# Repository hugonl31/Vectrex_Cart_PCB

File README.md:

# Vectrex cartridge PCBs

**Homemade Vectrex cartridges: the boards, ready to order, and a 3D-printed shell.**

<p align="center">

<br>

</p>

Cartridge boards for the Vectrex (GCE / Milton Bradley, 1982), designed in KiCad 9 to burn your own games -
homebrew, your own builds, or replacements for the original GCE releases - and a shell to put them in. Every
board has its KiCad files, Gerbers for a board maker, 3D renders, its copper layers and a schematic.

**Author:** Hugo Bokhorst ([@hugonl31](https://github.com/hugonl31)), also the author of
[Vectrex_EMU](https://github.com/hugonl31/Vectrex_EMU), which emulates these boards (bank switching, the
512K flash with its latch).<br>
**Documentation, schematics and renders:** made with Claude (Anthropic).

## The boards

| | Board | Chip | Size | For |
|---|---|---|---|---|
|  | [64K](boards/v1_27c512_64k) | 27C512 / W27C512 + DS2431 | 32 or 64 KB | any game up to 64 KB, with PB6 bank switching and an optional save chip |
|  | [8K GCE](boards/v1_28c64_8k_gce) | 28C64 EEPROM | 8 KB | the original GCE releases (4 or 8 KB); keep its jumper on write-protect |
|  | [512K v2](boards/v2_512k_flash) | SST39SF040 flash + 74HC377 latch | 512 KB | big bank-switched games, saving into the flash |

All boards share one outline (54 x 66 mm, 1.6 mm, ENIG, bevelled edge fingers), so they all fit the
[shell](case).

## How a Vectrex cartridge works

The cartridge port is a 36-finger edge connector. The Vectrex's 6809 CPU sees the cartridge in a **32 KB
window, $0000-$7FFF**: address lines A0-A14 and data lines D0-D7 go straight to the memory chip, with /CE and
/OE. Most original games fit in 4 or 8 KB and simply repeat through the window.

Bigger games switch **banks**: they swap which part of a larger chip is in the window. The port carries one
line the game controls for that, **PB6** (finger 35) from the Vectrex's 6522 VIA; the 64K board puts it on the
chip's A15 (two 32 KB banks). The 512K board adds a latch: a write into $0000-$3FFF stores three more address
bits, A16-A18, for 16 banks - see its [README](boards/v2_512k_flash).

The port also has R/W (writes), /CART, /HALT, /NMI and /IRQ, +5 V and GND. The pinout, as the boards use it
(odd fingers on one side, even on the other):

| Finger | Signal | Finger | Signal | Finger | Signal | Finger | Signal |
|---|---|---|---|---|---|---|---|
| 1 | /HALT | 10 | A11 | 19 | D0 | 28 | GND |
| 2 | +5V | 11 | A3 | 20 | D6 | 29 | A12 |
| 3 | A7 | 12 | /OE | 21 | D1 | 30 | R/W |
| 4 | +5V | 13 | A2 | 22 | D5 | 31 | A13 |
| 5 | A6 | 14 | A10 | 23 | D2 | 32 | /CART |
| 6 | A8 | 15 | A1 | 24 | D4 | 33 | A14 |
| 7 | A5 | 16 | /CE | 25 | GND | 34 | /NMI |
| 8 | A9 | 17 | A0 | 26 | D3 | 35 | PB6 |
| 9 | A4 | 18 | D7 | 27 | GND | 36 | /IRQ |

## The schematics

The boards were drawn directly in KiCad's PCB editor, so there are no KiCad schematic sheets. Each board's
`images/schematic.svg` is drawn from the board file itself: every part with its pin names, each pin ending in
its net name (pins with the same name are connected). It always matches the board, because it is made from it.

## Making one

1. **Order the board:** upload the board's `*-gerbers.zip` to JLCPCB, PCBWay or similar. 1.6 mm; ENIG (gold)
   is worth it for the edge fingers; ask for the 45 degree bevel on the finger edge if they offer it.
2. **Program the chip** with a TL866 / T48 (XGecu) or similar - each board's README says how.
3. **Solder** it (all through-hole chips, 1206 passives: easy by hand) and **print the [shell](case)**.

## Repository

| Path | |
|---|---|
| `boards/` | one folder per board: KiCad files, Gerbers, `images/` (renders, copper, schematic), a README |
| `case/` | the shell's STL files and renders |
| `libs/` | the KiCad footprints and symbols the boards use (edge connector, mounting holes, Vectrex logos) |

Open a board's `.kicad_pro` in KiCad 9; its library tables point to `libs/`.

## License

The board designs, the shell and the documentation: [CERN-OHL-P-2.0](LICENSE.md) - use, change, make and sell
them, keep the notice. Vectrex and its logo are trademarks of their owners; this project is not affiliated
with them. Datasheets and vendor 3D models are not included (the boards use KiCad's standard models).

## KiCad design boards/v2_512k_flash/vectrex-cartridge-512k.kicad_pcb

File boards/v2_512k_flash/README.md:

# Vectrex cartridge v2.0 - 512 KB flash with a bank latch

**Schematic:** [images/schematic.svg](images/schematic.svg) (drawn from the board's own connections) -
**copper:** [front](images/pcb_front.svg), [back](images/pcb_back.svg).

(The renders show the flash with its maker's 3D model in the socket. KiCad has no PLCC-32 socket model, so this
repository has a simple one of its own, `libs/3d/PLCC-32_THT-Socket.wrl` (made by `libs/3d/socket_wrl.py`); the board
file uses it.)

Built from the v1 64K board (`../v1_27c512_64k`): the same outline, edge fingers, Vectrex
logos (front and back), mounting holes, GND fill and "THIS SIDE UP". 54 x 66 mm, 2 layers.

| File | |
|---|---|
| `vectrex-cartridge-512k.kicad_pcb` / `.kicad_pro` | the board (open in KiCad 9) |
| `vectrex-cartridge-512k-gerbers.zip` | Gerbers + drill files for the board maker (JLCPCB, PCBWay...) |
| `images/` | 3D renders, the copper layers (`pcb_front.svg`, `pcb_back.svg`) and the schematic |
| `make_board.py` | builds the board from v1 (parts, nets, placement) - KiCad's Python |
| `routing/` | the router used (own, 45 degree / bundled lanes) and its plan - see Routing below |
| `silk.py` | the part names on the silkscreen |

## Circuit

| Part | Connections |
|---|---|
| **U1** SST39SF040 (512 KB flash) in a PLCC-32 socket | A0-A14, D0-D7 from the cartridge port. **A15 = PB6** (port pin 35, as on v1), **A16 / A17 / A18 = U2 Q0 / Q1 / Q2**. /CE = port pin 16. /OE = U3 (below). /WE = JP2. |
| **U2** 74HC377 bank latch (SOIC-20W) | D1-D3 = data bus D0-D2, CLKEN (pin 1) = R/W (port 30), CLK (pin 11) = U4 (/CART OR A14). A write to $0000-$3FFF stores the bank number. 1Q-3Q = A16-A18. D4-D8 (pins 8, 13, 14, 17, 18) are tied to GND: their outputs 4Q-8Q are not used, and five fewer data branches leave room for tidy routing. |
| **U3** 74HC00 (SOIC-14) | gate 1: E = NAND(/OE pin 12, /OE pin 12); gate 2: flash /OE = NAND(E, R/W). The flash only drives the bus when the CPU reads - the datasheet (table 4-1) says that with /OE low it may drive the bus even during a write, which would fight the CPU writing the bank number. Gates 3 and 4: inputs to GND. |
| **U4** 74HC1G32 OR gate (SOT-23-5) | latch clock = /CART OR A14: only writes to the lower 16 KB ($0000-$3FFF) reach the latch (pin 1 /CART, 2 A14, 3 GND, 4 out, 5 +5 V). |
| **R1** 3.3K pull-up | on PB6 = A15, as v1: a defined bank from power-on. |
| **JP2** solder jumper (flash /WE) | printed bridge **1-2: /WE = R/W, the game can save into the flash** (default). Cut 1-2 and bridge 2-3: /WE to +5 V = write-protected. |
| **C1-C4** 100 nF | one per chip. |

No DS2431 any more: high scores and settings are saved in the flash itself.

### How the game switches banks

The cartridge window is 32 KB ($0000-$7FFF). Bank = A18 A17 A16 A15:

* **A15** is PB6 of the VIA, as on v1: `DDRB` bit 6 output + `ORB` bit 6 (input = pulled high = 1).
* **A16-A18**: write a byte to **any address in $0000-$3FFF**; its bits 0-2 become A16-A18 at the end of the
  write cycle. `sta $0000` with A = bank >> 1 is enough. Writes to $4000-$7FFF never change the bank.
* The 74HC377 has no reset: after power-on (and after the Vectrex RESET button) A16-A18 can be anything.
  So the boot code - the cartridge header at $0000 and the first instructions until the latch is written -
  must be the same in every bank where the game can start: all 8 latch values with PB6 = 1 (the 8 odd
  banks). A game made for the 64K board already keeps such a shared area in both of its banks; here it becomes 8 copies.
* Code that switches banks must run from a place that is the same in both banks (as now), or from RAM.

### Saving into the flash (high scores, settings)

The flash's commands are writes to $5555 and $2AAA (only A0-A14 count). With U4, $5555 (A14 = 1) never
clocks the latch, but $2AAA (A14 = 0) does, and its data byte is always `$55` = A16-A18 **101**. So during
every program and erase command the flash sees bank A16-A18 = 101 - always the same bank, so:

* Keep the save area in **$4000-$7FFF of a bank with A16-A18 = 101** (banks 10 and 11, by PB6), in its own
  4 KB sector(s) - nothing else in those sectors.
* Byte program: `$AA`->$5555, `$55`->$2AAA, `$A0`->$5555, data -> address (~20 us).
  Sector erase: `$AA`->$5555, `$55`->$2AAA, `$80`->$5555, `$AA`->$5555, `$55`->$2AAA, `$30`->sector (~25 ms).
* The code doing this must run from RAM (the flash can't be read while it's busy), with PB6 set for the save
  bank; finish by writing the game's bank number back to $0000-$3FFF.
* 100 000 erase cycles per sector, ~100 years retention. Use two sectors in turn with a counter + checksum, so
  a power cut in the middle of a save always leaves the previous save.
* JP2 2-3 makes the flash read-only (e.g. a collector's copy).

## Parts (digikey.at, October 2026)

| Ref | Part | DigiKey no. | Price |
|---|---|---|---|
| U1 | Microchip SST39SF040-55-4C-NHE-T (512 KB, PLCC-32, 55 ns) | SST39SF040-55-4C-NHE-TCT-ND | 2.58 EUR |
| U1 socket | Assmann A-CCS 032-Z-T (PLCC-32, through hole) | AE11106-ND | 1.86 EUR |
| U2 | TI SN74HC377DWR (SOIC-20W) - or SN74HCT377DW (see below) | 296-9818-1-ND | 0.76 EUR |
| U3 | TI SN74HC00DR (SOIC-14) - or SN74HCT00DR | search "SN74HC00DR" | 0.35 EUR |
| U4 | TI SN74AHCT1G32DBVR (SOT-23-5) | search "SN74AHCT1G32DBVR" | ~0.3 EUR |
| R1 | 3.3 kOhm 1206 | as v1 | |
| C1-C4 | 100 nF 1206 | as v1 | |
| | PLCC-32 to DIP-32 adapter for the XGecu programmer | AliExpress / eBay | |

**HC or HCT?** The 6809 and the VIA are NMOS chips: their "high" can be as low as 2.4 V, below what 74HC inputs
need at 5 V (3.5 V). In practice it usually works (they pull up close to 5 V with the light cartridge load), but
the HCT versions (TTL input levels, same pins, same price range) are the safe choice for all three logic chips.

The SST39SF020A (256 KB) and SST39SF010A (128 KB) fit the same socket: with them A18 (and A17) are not
connected inside the chip, the banks just repeat.

## Routing

The traces leave every edge finger straight up, then run as bundled lanes in 0 / 45 / 90 degree steps
with as few bends as possible; fingers without a function (/HALT 1, /NMI 34, /IRQ 36) have no copper at
all, and the two +5 V fingers (2 and 4) are joined by a wide track. The PLCC socket is turned 180 degrees
and placed 4 mm higher than in the first version, so the address bus reaches it from inside. GND: a fill
on both sides, joined by stitching vias wherever a piece of it would otherwise be cut off.

## Checks

* KiCad 9 DRC with the project's rules (0.152 mm clearance, +5 V and GND 0.254 mm / 0.61 mm tracks): no
  unconnected items, no clearance errors. Remaining, accepted (as v1): the edge fingers share one solder-mask
  opening; a silkscreen label touches a finger's pin number and JP2's "3" touches its pad; the edge connector's
  and KiCad library footprints' "differs from library" notes.
* Every piece of the GND fill (front and back) is tied to ground - checked with a connectivity pass over the
  pads, tracks, vias and fills.
* No vias under the back's parts legend.
* No tracks in the fingers' contact area (both sides): tracks only meet a finger at its top 1.6 mm.
* Pinouts checked against the datasheets: SST39SF040 (DS20005022, PLCC-32 = JEDEC numbering), SN74HC377
  (SCLS307D), SN74HC00 (SCLS181H).
* Timing to confirm on the first board: the latch clocks on /CART rising (end of the write); the 6809 holds
  the data ~30 ns after E falls, the 74HC377 needs ~5 ns hold - fine on paper, worth a first test with a
  bank-switch test cartridge before building more.

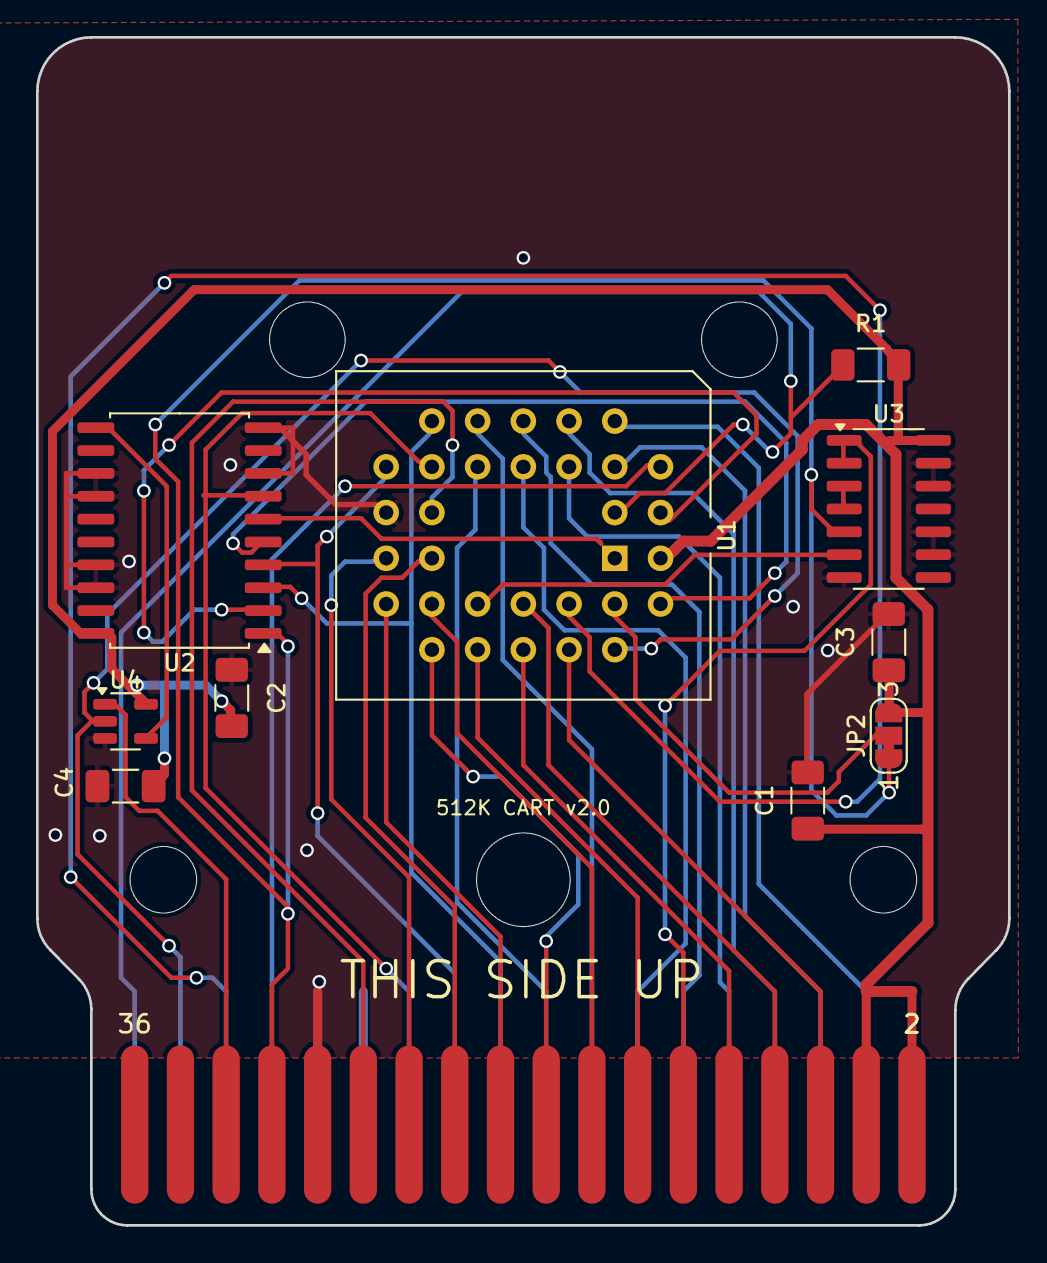
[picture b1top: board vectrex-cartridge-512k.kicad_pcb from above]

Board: 2 copper layers, 54.0 x 66.0 mm, 18 parts (1 on the bottom side), 37 nets.

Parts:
C1, C2, C3, C4: 100nF; C1_hand_1206_3216Metric_Pad1.33x1.80mm_HandSolder
CON1: vectrex-edge-connector; vectrex-edge-connector-thinner-no-soldermask
G1: LOGO; vectrex-us-soldermask
G3: LOGO; vectrex-uk-soldermask
H1, H3: 3.7mm; Mounting_Hole_D3.7mm
H2: 5.2mm; Mounting_Hole_D5.2mm
H4, H5: 4.2mm; Mounting_Hole_D4.2mm
JP2: FLASH /WE; SolderJumper-3_P1.3mm_Bridged12_RoundedPad1.0x1.5mm_NumberL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
R1: 3.3K; R1_1206_3216Metric_Pad1.30x1.75mm_HandSolder
U1: SST39SF040 (PLCC-32 socket); PLCC-32_THT-Socket
U2: 74HC377; SOIC-20W_7.5x12.8mm_P1.27mm
U3: 74HC00; SOIC-14_3.9x8.7mm_P1.27mm
U4: 74HC1G32; SOT-23-5

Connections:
+5V: C1.1, C2.1, C3.1, C4.1, CON1.2, CON1.4, JP2.3, R1.2, U1.32, U2.20, U3.14, U4.5
BA16: U1.2, U2.2
BA17: U1.30, U2.5
BA18: U1.1, U2.6
C_A0: CON1.17, U1.12
C_A1: CON1.15, U1.11
C_A2: CON1.13, U1.10
C_A3: CON1.11, U1.9
C_A4: CON1.9, U1.8
C_A5: CON1.7, U1.7
C_A6: CON1.5, U1.6
C_A7: CON1.3, U1.5
C_A8: CON1.6, U1.27
C_A9: CON1.8, U1.26
C_A10: CON1.14, U1.23
C_A11: CON1.10, U1.25
C_A12: CON1.29, U1.4
C_A13: CON1.31, U1.28
C_A14: CON1.33, U1.29, U4.2
C_D0: CON1.19, U1.13, U2.3
C_D1: CON1.21, U1.14, U2.4
C_D2: CON1.23, U1.15, U2.7
C_D3: CON1.26, U1.17
C_D4: CON1.24, U1.18
C_D5: CON1.22, U1.19
C_D6: CON1.20, U1.20
C_D7: CON1.18, U1.21
E: U3.3, U3.4
FL_OE: U1.24, U3.6
FL_WE: JP2.2, U1.31
GND: C1.2, C2.2, C3.2, C4.2, CON1.25, CON1.27, CON1.28, U1.16, U2.8, U2.10, U2.13, U2.14, U2.17, U2.18, U3.7, U3.9, U3.10, U3.12, U3.13, U4.3
LCLK: U2.11, U4.4
V-CART: CON1.32, U4.1
V-CE: CON1.16, U1.22
V-OE: CON1.12, U3.1, U3.2
V-PB6: CON1.35, R1.1, U1.3
V-RW: CON1.30, JP2.1, U2.1, U3.5

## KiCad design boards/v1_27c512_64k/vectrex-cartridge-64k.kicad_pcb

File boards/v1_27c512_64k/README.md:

# 64K cartridge - 27C512 / W27C512 with a DS2431 save chip

The main board: any Vectrex game up to 64 KB, on a 27C512 EPROM or a Winbond W27C512 (electrically erasable:
no UV lamp, the programmer erases it). 54 x 66 mm, 2 layers, 1.6 mm, ENIG, bevelled edge fingers.

**Schematic:** [images/schematic.svg](images/schematic.svg) (drawn from the board's own connections) -
**copper:** [front](images/pcb_front.svg), [back](images/pcb_back.svg).

| File | |
|---|---|
| `vectrex-cartridge-64k.kicad_pcb` / `.kicad_pro` | the board (KiCad 9) |
| `vectrex-cartridge-64k-gerbers.zip` | Gerbers + drill files, ready for JLCPCB, PCBWay... |
| `images/` | renders, copper layers, schematic |

## Parts

| Ref | Part | |
|---|---|---|
| U1 | 27C512 or W27C512 (DIP-28) | the game; a socket is handy while developing |
| U2 | DS2431 (TO-92) | optional: a 1 Kbit 1-Wire EEPROM on PB6, for high scores and settings |
| R1 | 3.3 kOhm, 1206 | pull-up on PB6 |
| C1 | 100 nF, 1206 | decoupling |
| JP1 | solder jumper, 3 pads | 32KB / 64KB (below) |

## How it works

The Vectrex's cartridge window is 32 KB ($0000-$7FFF): the port's A0-A14. A 27C512 holds 64 KB, so its
fifteenth address line, **A15**, picks one of two 32 KB halves (banks). **JP1** sets it:

* **32KB** (A15 to GND): a plain 32 KB (or smaller) game. Program the image into the chip's first half.
* **64KB** (A15 to PB6): a bank-switched 64 KB game. PB6 is a line of the Vectrex's 6522 VIA that reaches the
  cartridge port (pin 35); the game switches banks by driving it (DDRB bit 6 as an output, ORB bit 6 the bank).
  **R1** pulls PB6 up, so while it is still an input it reads 1: the cartridge powers up in bank 1. The boot
  code must be where the game starts (the usual 64 KB images are laid out that way).

**U2, the DS2431**, sits on PB6 too: a 1-Wire memory (1024 bits) a game can talk to through that same line,
for saving high scores. Leave it out if the game doesn't use it.

The EPROM's /CE and /OE come straight from the port (pins 16 and 12), its data lines D0-D7 and address lines
A0-A14 too. Nothing else is needed: no logic chips.

## Programming

A TL866 / T48 (XGecu) or any programmer that does 27C512s. A W27C512 is erased by the programmer (it needs
its 14 V erase voltage), so no UV eraser. Program the game's .bin as it is: a 32 KB image into the first
half (jumper on 32KB), a 64 KB image whole (jumper on 64KB).

## Ordering

Upload `vectrex-cartridge-64k-gerbers.zip` to the board maker. 1.6 mm, ENIG (gold) is worth it for the edge
fingers, with a 45 degree chamfer on the finger edge if they offer it ("edge connector bevelling").

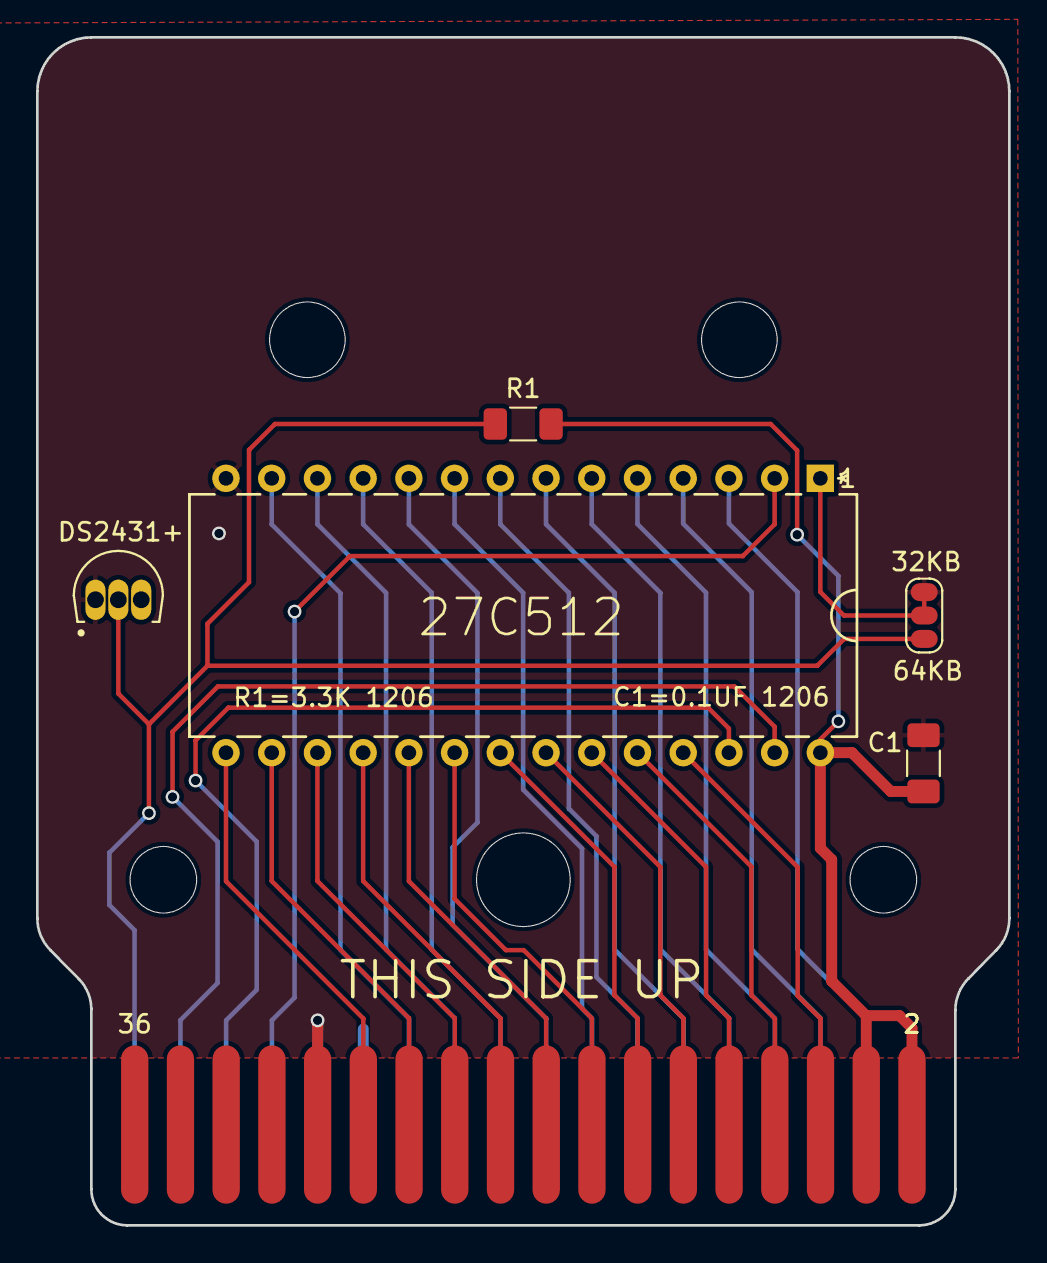
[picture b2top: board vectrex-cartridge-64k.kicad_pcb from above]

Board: 2 copper layers, 54.0 x 66.0 mm, 8 parts (1 on the bottom side), 2 nets.

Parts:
CON1: vectrex-edge-connector; vectrex-edge-connector-thinner-no-soldermask
G1: LOGO; vectrex-us-soldermask
G3: LOGO; vectrex-uk-soldermask
H1, H3: 3.7mm; Mounting_Hole_D3.7mm
H2: 5.2mm; Mounting_Hole_D5.2mm
H4, H5: 4.2mm; Mounting_Hole_D4.2mm

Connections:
+5V: CON1.2, CON1.4
GND: CON1.25, CON1.27, CON1.28
